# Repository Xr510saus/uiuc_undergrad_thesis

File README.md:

# uiuc_undergrad_thesis

## Project description

For my undergraduate (UIUC) thesis, I designed a cable-driven soft robot to crawl on 2D surfaces. This repo contains the entire history of the project, which lasted over my final two semesters at UIUC, starting from my funding application, through my progress reports, and finally ending at the FINAL DELIVERABLES directory, which contains my actual thesis and the slides I presented at the Undergraduate Thesis Symposium.

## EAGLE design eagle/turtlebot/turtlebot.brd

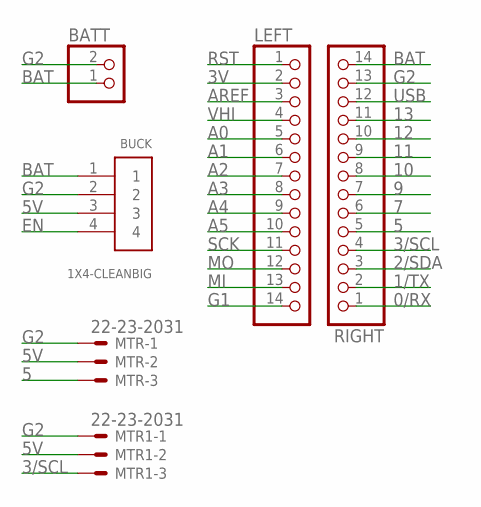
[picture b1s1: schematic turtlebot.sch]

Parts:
BATT: JST_2PIN-THM-RA; JST-PH-2-THM-RA
BUCK: 1X4-CLEANBIG; 1X04-CLEANBIG
LEFT: MICROBUILDER_HEADER-1X14; MICROBUILDER_1X14_ROUND70
MTR, MTR1: 22-23-2031
RIGHT: MICROBUILDER_HEADER-1X14; MICROBUILDER_1X14_ROUND70

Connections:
0/RX: RIGHT.1
1/TX: RIGHT.2
2/SDA: RIGHT.3
3/SCL: MTR1.3, RIGHT.4
3V: LEFT.2
5: MTR.3, RIGHT.5
5V: BUCK.3, MTR.2, MTR1.2
7: RIGHT.6
9: RIGHT.7
10: RIGHT.8
11: RIGHT.9
12: RIGHT.10
13: RIGHT.11
A0: LEFT.5
A1: LEFT.6
A2: LEFT.7
A3: LEFT.8
A4: LEFT.9
A5: LEFT.10
AREF: LEFT.3
BAT: BATT.1 (2), BUCK.1, RIGHT.14
EN: BUCK.4
G1: LEFT.14
G2: BATT.2 (1), BUCK.2, MTR.1, MTR1.1, RIGHT.13
MI: LEFT.13
MO: LEFT.12
RST: LEFT.1
SCK: LEFT.11
USB: RIGHT.12
VHI: LEFT.4

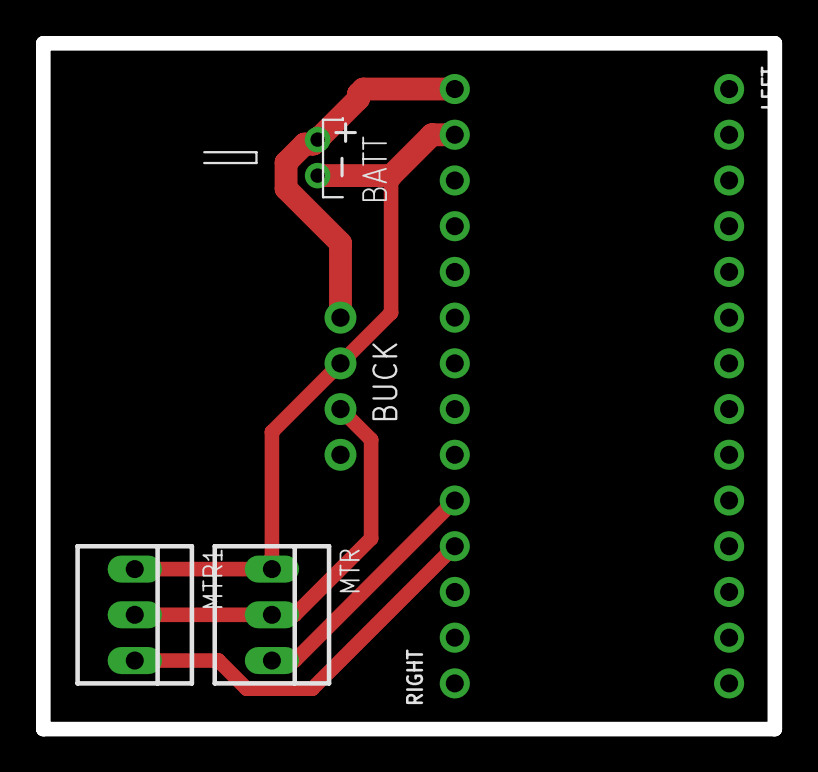
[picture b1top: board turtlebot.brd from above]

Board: 2 copper layers, 40.6 x 38.1 mm, 6 parts (0 on the bottom side), 5 nets.

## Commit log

2023-12-19 Copying undergrad thesis finals to git
